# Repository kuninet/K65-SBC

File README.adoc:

= 6502CPU シングルボードコンピューター =

== 概要 ==
* 6502CPUを使用したシングルボードコンピューターです。

image::img/K65-SBC-BOARD.jpg[]
image::K65-SBC-外観.png[]

== 特徴 ==
* Grantさんが公開している 6502コンピューターとアドレスを合わせてありますので、同じソフトが動きます。

== ディレクトリの説明 ==
* 回路図はimgディレクトリに入っています。
* KiCADデータはKiCadディレクトリです。
** 回路図の6502のシンボルは https://github.com/Alarm-Siren/6502-kicad-library[6502 KiCad Library]の成果を使用させていただきました。

* srcディレクトリにUniversal Monitor (Electrelicさん作)の移植用ソースを添付します。MC6850対応ドライバーを含んでいます。アセンブル済みのhexファイルも添付します。
** 28C256(256k)タイプのEEPROMへ、IntelHex形式のファイルから書き込んで使用してください。
** 書き込みの際、TL866CSを使う場合は、以下のように$Fxxxは$7xxxへ読み替える指定をしてください。

image::img/TL866CS-1.png[]

== 参考 ==
* Grant's 8-chip (or 7-chip) 6502 computer
** http://searle.x10host.com/6502/Simple6502.html
* Universal Monitor (Electrelicさん)
** https://electrelic.com/electrelic/node/1318
* 6502 KiCad Library
** https://github.com/Alarm-Siren/6502-kicad-library

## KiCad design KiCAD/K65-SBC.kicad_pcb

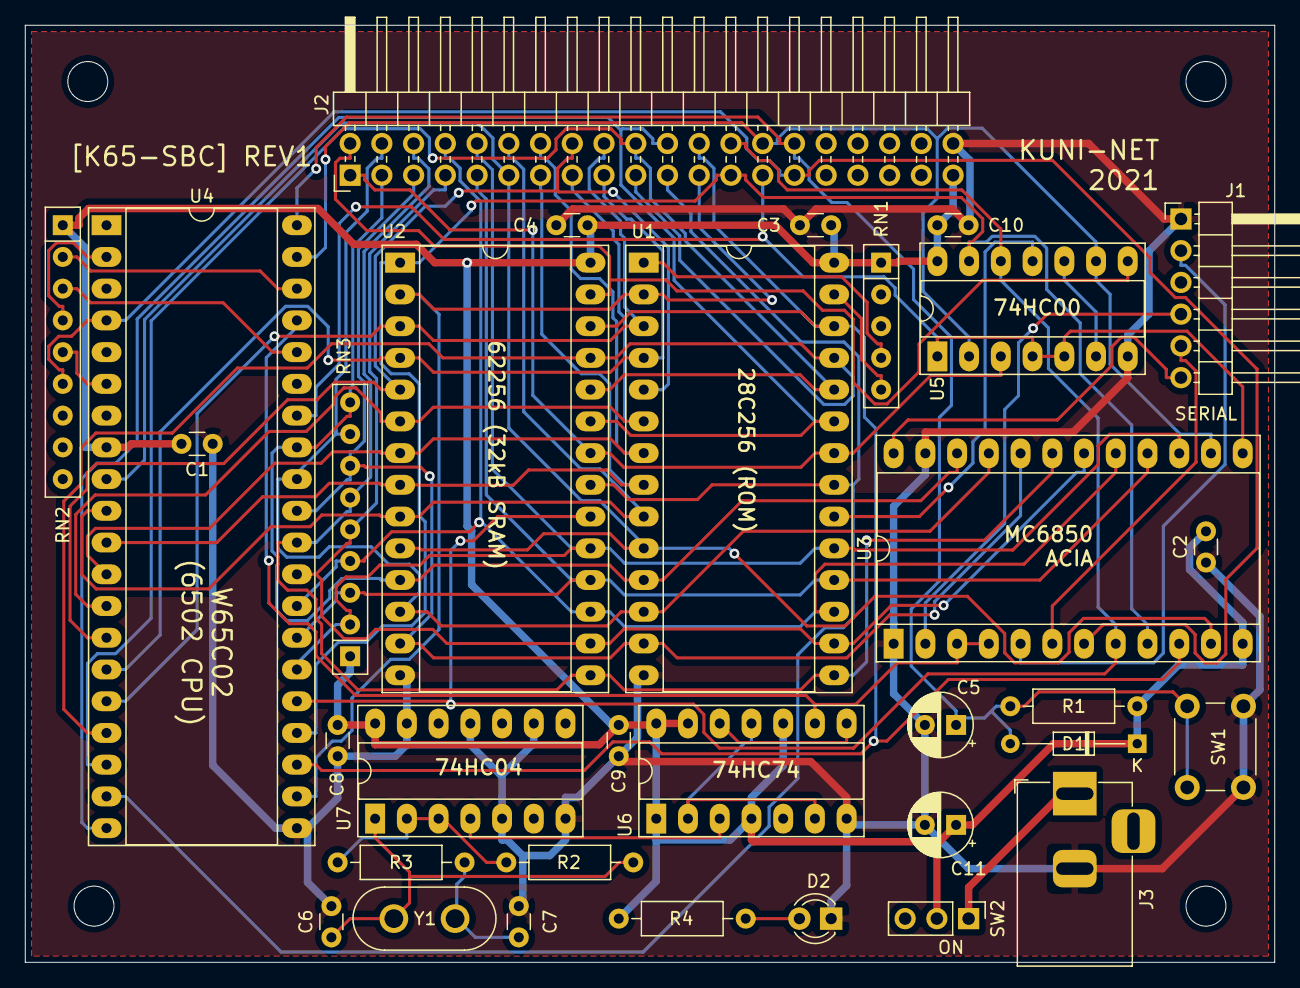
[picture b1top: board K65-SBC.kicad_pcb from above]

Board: 2 copper layers, 100.0 x 75.0 mm, 37 parts (0 on the bottom side), 53 nets.

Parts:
C1, C2, C3, C4, C8, C9, C10: 0.1u; C_Disc_D3.0mm_W1.6mm_P2.50mm
C5, C11: 10u; CP_Radial_D5.0mm_P2.50mm
C6, C7: 22p; C_Disc_D3.0mm_W1.6mm_P2.50mm
D1: 1N4418; D_DO-34_SOD68_P10.16mm_Horizontal
D2: POWER LED; LED_D3.0mm
H1, H2, H3, H4: MountingHole; MountingHole_3.2mm_M3
J1: SERIAL CON; PinHeader_1x06_P2.54mm_Horizontal
J2: SBC6303 BUS; PinHeader_2x20_P2.54mm_Horizontal
J3: DC JACK; BarrelJack_Horizontal
R1: 4.7k; R_Axial_DIN0207_L6.3mm_D2.5mm_P10.16mm_Horizontal
R2: 1M; R_Axial_DIN0207_L6.3mm_D2.5mm_P10.16mm_Horizontal
R3: 1k; R_Axial_DIN0207_L6.3mm_D2.5mm_P10.16mm_Horizontal
R4: 470; R_Axial_DIN0207_L6.3mm_D2.5mm_P10.16mm_Horizontal
RN1: 10k; R_Array_SIP5
RN2, RN3: 10k; R_Array_SIP9
SW1: RESET; SW_PUSH_6mm
SW2: POWER SW; PinHeader_1x03_P2.54mm_Vertical
U1: 28C256; DIP-28_W15.24mm_Socket_LongPads
U2: 62256; DIP-28_W15.24mm_Socket_LongPads
U3: MC6850; DIP-24_W15.24mm_Socket_LongPads
U4: W65C02SxP; DIP-40_W15.24mm_Socket_LongPads
U5: 74HC00; DIP-14_W7.62mm_Socket_LongPads
U6: 74HC74; DIP-14_W7.62mm_Socket_LongPads
U7: 74HC04; DIP-14_W7.62mm_Socket_LongPads
Y1: 7.3728MHz; Crystal_HC50_Vertical

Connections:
/A0: J2.11, U1.10, U2.10, U3.11, U4.9
/A1: J2.12, U1.9, U2.9, U4.10
/A2: J2.13, U1.8, U2.8, U4.11
/A3: J2.14, U1.7, U2.7, U4.12
/A4: J2.15, U1.6, U2.6, U4.13
/A5: J2.16, U1.5, U2.5, U4.14
/A6: J2.17, U1.4, U2.4, U4.15
/A7: J2.18, U1.3, U2.3, U4.16
/A8: J2.19, U1.25, U2.25, U4.17
/A9: J2.20, U1.24, U2.24, U4.18
/A10: J2.21, U1.21, U2.21, U4.19
/A11: J2.22, U1.23, U2.23, U4.20
/A12: J2.23, U1.2, U2.2, U4.22
/A13: J2.24, U1.26, U2.26, U3.10, U4.23
/A14: J2.25, U2.1, U3.9, U4.24, U5.13
/A15: J2.26, U2.20, U3.8, U4.25, U5.12
/CLK: U3.3, U3.4, U4.37, U6.9
/D0: J2.3, RN3.9, U1.11, U2.11, U3.22, U4.33
/D1: J2.4, RN3.8, U1.12, U2.12, U3.21, U4.32
/D2: J2.5, RN3.7, U1.13, U2.13, U3.20, U4.31
/D3: J2.6, RN3.6, U1.15, U2.15, U3.19, U4.30
/D4: J2.7, RN3.5, U1.16, U2.16, U3.18, U4.29
/D5: J2.8, RN3.4, U1.17, U2.17, U3.17, U4.28
/D6: J2.9, RN3.3, U1.18, U2.18, U3.16, U4.27
/D7: J2.10, RN3.2, U1.19, U2.19, U3.15, U4.26
/PH2: J2.28, U3.14, U4.39, U5.2, U5.9
/R~W: J2.27, U3.13, U4.34, U5.1, U5.4, U5.5
/~IRQ: J2.29, RN2.6, U3.7, U4.4
/~RD: J2.1, U1.22, U2.22, U5.3
/~RES: C5.1, D1.2, J2.30, R1.2, SW1.2, U4.40
/~WR: J2.2, U2.27, U5.8
GND: C1.1, C2.1, C3.1, C4.1, C5.2, C6.2, C7.2, C8.1, C9.1, C10.1, C11.2, D2.1, J1.1, J2.40, J3.2, SW1.1, U1.14, U2.14, U3.1, U3.23, U4.21, U5.7, U6.7, U7.5, U7.7, U7.9, U7.11, U7.13
unnamed: C6.1, R2.2, U7.1, Y1.1
unnamed: C7.1, R3.2, Y1.2
unnamed: D2.2, R4.2
unnamed: J1.2, U3.5
unnamed: J1.4, U3.2
unnamed: J1.5, U3.6
unnamed: J1.6, U3.24
unnamed: J3.1, SW2.1
unnamed: R2.1, R3.1, U7.2, U7.3
unnamed: RN1.4, U1.1
unnamed: RN1.5, U1.27
unnamed: RN2.2, U4.38
unnamed: RN2.3, U4.36
unnamed: RN2.4, U4.2
unnamed: RN2.5, U4.6
unnamed: U1.20, U5.11
unnamed: U5.6, U5.10
unnamed: U6.3, U7.4
unnamed: U6.2, U6.6, U6.11
unnamed: U6.8, U6.12
VCC: C1.2, C2.2, C3.2, C4.2, C8.2, C9.2, C10.2, C11.1, D1.1, J2.39, R1.1, R4.1, RN1.1, RN2.1, RN3.1, SW2.2, U1.28, U2.28, U3.12, U4.8, U5.14, U6.1, U6.4, U6.10, U6.13, U6.14, U7.14

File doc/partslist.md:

# K65-SBC 部品表

|部品番号|仕様|数量|備考|
|:---:|:---|---:|:---|
|C1-C4,C8,C9,C10|0.1uF|7|積層セラミックコンデンサ|
|C5|10uF|1|電解コンデンサ|
|C6,C7|22pF|2|積層セラミックコンデンサ|
|C11|10uF|1|電解コンデンサ|
|D1|1N4418|1|小信号ダイオード|
|D2|3mm LED|1|POWER LED|
|J1|1x6L型型ピンヘッダ|1|SERIAL CON|
|J2|2x20(40ピン)L型ボックスヘッダ|1|SBC6303 BUS|
|J3||1|DC JACK|
|R1|4.7k|1|カーボーン抵抗器|
|R2|1M|1|カーボン抵抗器|
|R3|1k|1|カーボン抵抗器|
|R4|470|1|LED用カーボン抵抗|
|RN1|10k|1|4素子集合抵抗器|
|RN2,3|10k|2|8素子集合抵抗器|
|SW1|タクトスイッチ|1|RESET|
|SW2|基板用スライドSW|1|POWER SW|
|U1|28C256|1|フラッシュROM32kB|
|U2|62256|1|SRAM 32k|
|U3|MC6850|1|ACIAシリアルIC|
|U4|W65C02SxP|1|6502CPU|
|U5|74HC00|1|NANDゲート|
|U6|74HC74|1|D-FF|
|U7|74HC04|1|NOTゲート|
|Y1|7.3728MHz|1|水晶振動子|
||40ピンICソケット|1||
||28ピンICソケット|2||
||24ピンICソケット|1||
||14ピンICソケット|3||

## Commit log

2020-04-10 Update LICENSE
2020-04-10 各種ファイルコミット
2020-04-10 サンブル説明追加
2020-04-10 アセンブリ関係追記
2020-04-20 サンプルソース追加
2020-04-29 サンプロブログラム追加・修正
2020-06-21 回路図整備、部品表作成
2020-06-21 回路図差し替え
2021-12-18 REV1ガーバーデータ出力
